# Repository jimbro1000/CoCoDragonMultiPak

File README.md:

# Dragon MultiPak Interface #

This repository contains the designs for a Dragon 32/64
multipak interface based closely on the TRS-80 Color 
Computer multipak system.

The board allows up to four expansion cartridges to be
connected instead of the normal single slot.

The original CoCo MultiPak is a poor fit with the 
Dragon, this design slims down the interface to
ensure it will work with the Dragon cartridge port.

The CoCo also includes a -5V rail connection which
the Dragon substitutes with an additional +12V rail.
Both cartridge pins are unconnected in this design
as a precaution

## Power Supply ##

For casual use the +5V supplied by the Dragon PSU
should suffice but could become marginal under load.
This board includes an independent power supply that
can supplement the 5V current supply, or even run a
modified Dragon board if additional voltages are not
required.

The power board requires either a 12-15V AC input or
a 15-18V DC input (polarity of the connector is not
important). If 12V is not required (or critical) a 
lower rated DC power adapter can be used.

By default the 12V rail is rated at 0.5A but the 
DC-DC converter on the board can easily be swapped
for a higher rated compatible component.

## GAL Programming ##

A comprehensive set of source definitions for the 
GAL 16V8 chip at IC13 are available on github:
https://github.com/TheLittleEngineers/CoCoDragon-MultiPakInterface-CC-Multi-Pak_Version_1.2/tree/master/PAL_GAL

The GAL programs have been tested for use in a
CoCo but not with a Dragon - memory mapping should
be compatible so no issue is envisaged

Until testing is completed and the programming
conirmed the GAL programs should be treated as untried
in this context.

### GAL Equations

Note this is written in CUPL.

AND is &, OR is # and XOR is $

```CUPL
/** INPUT **/
PIN [2..9] = [A7..0];   /* address bus lsb */
PIN 1 = !FFXX;          /* mapped address range */
PIN 11 = RW;            /* RnW */
PIN 12 = E;             /* Quadrature clock E */
PIN 13 = Q;             /* Quadrature clock Q */
PIN 17 = !CSEL;         /* Cartridge select */
PIN 18 = !SLEB;         /* Device select disable */

/** OUTPUT **/
PIN 14 = !DBEN;         /* Enable data buffer */
PIN 15 = !IOR;          /* Read device select latch */
PIN 16 = !IOW;          /* Write device select latch */

/** EQUATIONS **/
FIELD ADDRESS = [A7..0];

MATCH = ADDRESS:[7F];

LATCH = MATCH & E & FFXX;

EN = ADDRESS:[40..7F] & FFXX;

DBEN = EN # SLEB # CSEL;

IOR = LATCH & RW;

IOW = LATCH & !Q & !RW;
```

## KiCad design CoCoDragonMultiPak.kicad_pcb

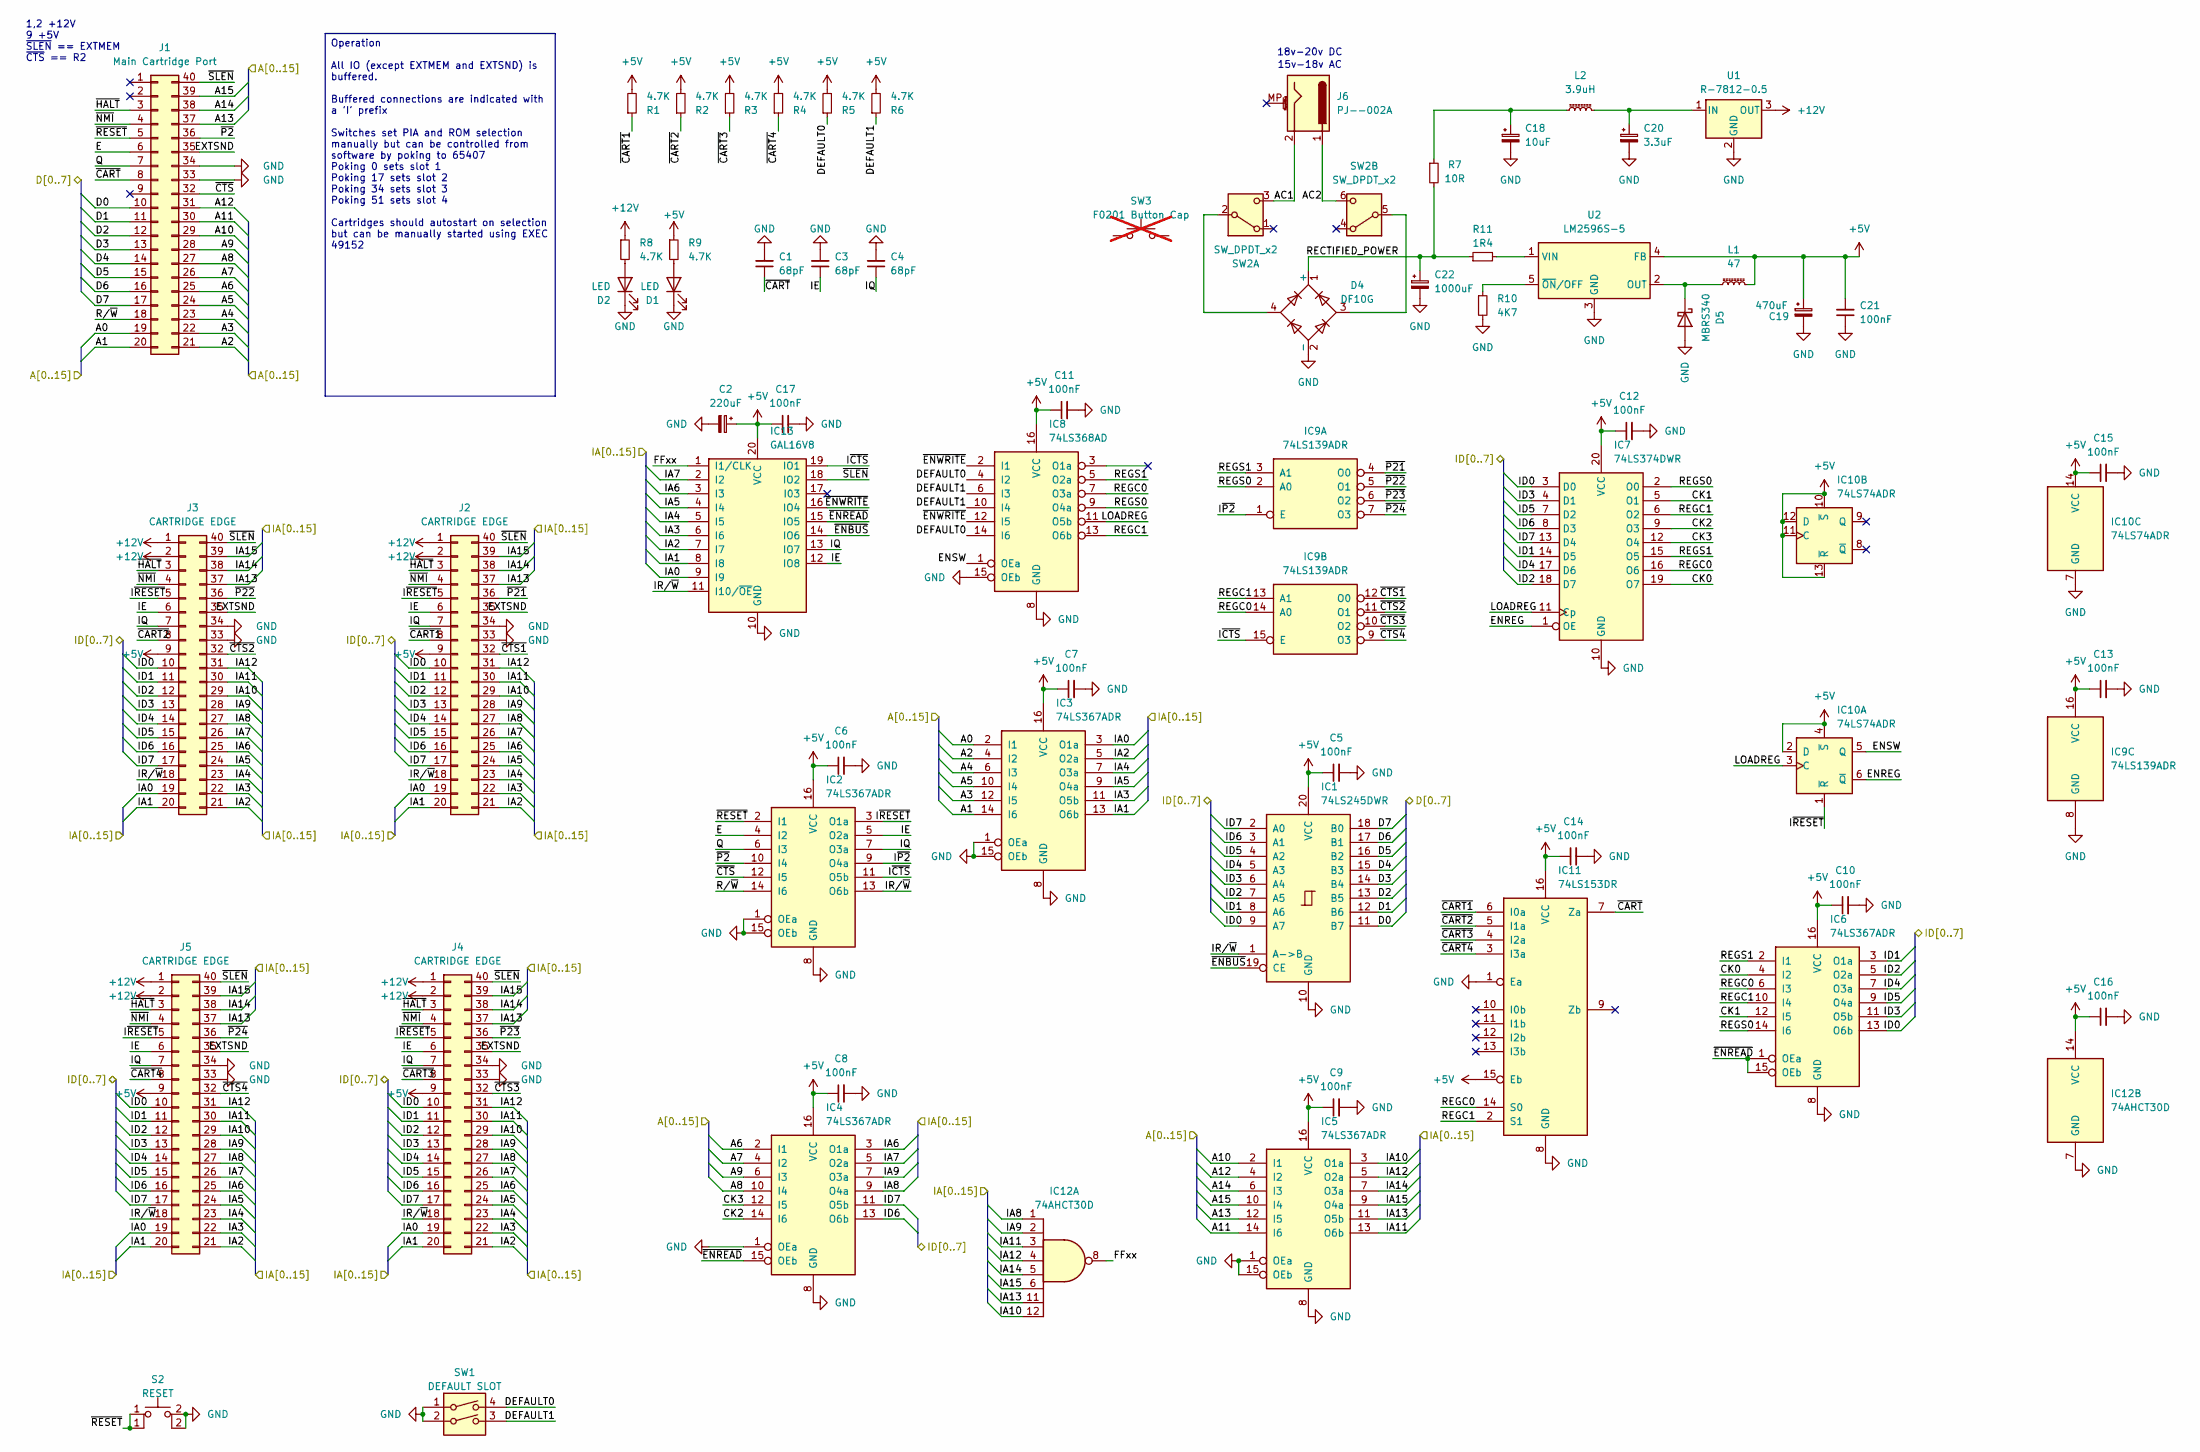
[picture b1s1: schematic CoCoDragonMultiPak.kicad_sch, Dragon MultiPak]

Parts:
C1, C3, C4: 68pF; C_0805_2012Metric_Pad1.18x1.45mm_HandSolder; LCSC C2363555
C2: 220uF; CP_Elec_6.3x5.4_Nichicon; LCSC C2162905
C5, C6, C7, C8, C9, C10, C11, C12, C13, C14, C15, C16, C17: 100nF; C_0805_2012Metric_Pad1.18x1.45mm_HandSolder; LCSC C2215757
C18: 10uF; CP_Elec_4x5.4; LCSC C213486
C19: 470uF; CP_Elec_6.3x5.4_Nichicon
C20: 3.3uF; CP_Elec_4x5.8; LCSC C413673
C21: 100nF; C_0805_2012Metric_Pad1.18x1.45mm_HandSolder
C22: 1000uF; CP_Elec_10x10.5
D1, D2: LED; LED_0805_2012Metric_Pad1.15x1.40mm_HandSolder; LCSC C5353441
D4: DF10G; Diode_Bridge_DIP-4_W7.62mm_P5.08mm; DigiKey 641-1340-5-ND
D5: MBRS340; D_SMC_Handsoldering; DigiKey 112-VS-MBRS340-M3/9ATCT-ND
IC1: 74LS245DWR; SOIC-20W_7.5x12.8mm_P1.27mm; DigiKey 296-1125-1-ND
IC2, IC3, IC4, IC5, IC6: 74LS367ADR; SOIC-16_3.9x9.9mm_P1.27mm; DigiKey 296-3700-1-ND
IC7: 74LS374DWR; SOIC-20W_7.5x12.8mm_P1.27mm; DigiKey 296-14894-1-ND
IC8: 74LS368AD; SOIC-16_3.9x9.9mm_P1.27mm; DigiKey 296-33998-5-ND
IC9: 74LS139ADR; SOIC-16_3.9x9.9mm_P1.27mm; DigiKey 296-31850-1-ND
IC10: 74LS74ADR; SOIC-14_3.9x8.7mm_P1.27mm; DigiKey 296-14899-1-ND
IC11: 74LS153DR; SOIC-16_3.9x9.9mm_P1.27mm; DigiKey 296-SN74LS153DRCT-ND
IC12: 74AHCT30D; SOIC-14_3.9x8.7mm_P1.27mm; DigiKey 1727-74AHCT30D-Q100JCT-ND
IC13: GAL16V8; DIP-20_W7.62mm_LongPads; DigiKey ATF16V8C-7PU-ND
J1: Main Cartridge Port; EdgeConnector
J2, J3, J4, J5: CARTRIDGE EDGE; CardSocket; DigiKey 3-583717-1-ND
J6: PJ--002A; Power_BarrelJack; DigiKey CP-002A-ND
L1: 47; L_Taiyo-Yuden_MD-4040; LCSC C520312
L2: 3.9uH; L_1812_4532Metric; LCSC C5603190
R1, R2, R3, R4, R5, R6, R8, R9: 4.7K; R_0805_2012Metric_Pad1.20x1.40mm_HandSolder; LCSC C269341
R7: 10R; R_2512_6332Metric; LCSC C2992634
R10: 4K7; R_0805_2012Metric_Pad1.20x1.40mm_HandSolder; LCSC C706300
R11: 1R4; RES_SM6227_STP; LCSC C4075361
S2: RESET; SW_PUSH_6mm; DigiKey 450-1644-ND
SW1: DEFAULT SLOT; SW_DIP_SPSTx02_Slide_6.7x6.64mm_W7.62mm_P2.54mm_LowProfile; DigiKey CT1952MST-ND
SW2: SW_DPDT_x2; ALPS_DPDT_SPUN190900
SW3: F0201 Button Cap; SW_PUSH-12mm; DigiKey 401-1215-ND; not fitted
U1: R-7812-0.5; Converter_DCDC_RECOM_R-78E-0.5_THT; DigiKey 945-1032-ND
U2: LM2596S-5; TO-263-5_TabPin3; DigiKey LM2596S-5.0/NOPB-ND

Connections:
+5V: C2.1, C5.1, C6.1, C7.1, C8.1, C9.1, C10.1, C11.1, C12.1, C13.1, C14.1, C15.1, C16.1, C17.1, C19.1, C21.2, IC1.20 (VCC), IC2.16 (VCC), IC3.16 (VCC), IC4.16 (VCC), IC5.16 (VCC), IC6.16 (VCC), IC7.20 (VCC), IC8.16 (VCC), IC9.16 (VCC), IC10.2 (D), IC10.4 (~S), IC10.10 (~S), IC10.11 (C), IC10.12 (D), IC10.13 (~R), IC10.14 (VCC), IC11.15 (Eb), IC11.16 (VCC), IC12.14 (VCC), IC13.20 (VCC), J2.9, J3.9, J4.9, J5.9, L1.2, R1.2, R2.2, R3.2, R4.2, R5.2, R6.2, R9.1, U2.4 (FB)
+12V: J2.1, J2.2, J3.1, J3.2, J4.1, J4.2, J5.1, J5.2, R8.1, U1.3 (OUT)
/A0: IC3.2 (I1), J1.19
/A1: IC3.14 (I6), J1.20
/A2: IC3.4 (I2), J1.21
/A3: IC3.12 (I5), J1.22
/A4: IC3.6 (I3), J1.23
/A5: IC3.10 (I4), J1.24
/A6: IC4.2 (I1), J1.25
/A7: IC4.4 (I2), J1.26
/A8: IC4.10 (I4), J1.27
/A9: IC4.6 (I3), J1.28
/A10: IC5.2 (I1), J1.29
/A11: IC5.14 (I6), J1.30
/A12: IC5.4 (I2), J1.31
/A13: IC5.12 (I5), J1.37
/A14: IC5.6 (I3), J1.38
/A15: IC5.10 (I4), J1.39
/AC1: J6.2, SW2.3 (C)
/AC2: J6.1, SW2.6 (C)
/CK0: IC6.4 (I2), IC7.19 (O7)
/CK1: IC6.12 (I5), IC7.5 (O1)
/CK2: IC4.14 (I6), IC7.9 (O3)
/CK3: IC4.12 (I5), IC7.12 (O4)
/D0: IC1.11 (B7), J1.10
/D1: IC1.12 (B6), J1.11
/D2: IC1.13 (B5), J1.12
/D3: IC1.14 (B4), J1.13
/D4: IC1.15 (B3), J1.14
/D5: IC1.16 (B2), J1.15
/D6: IC1.17 (B1), J1.16
/D7: IC1.18 (B0), J1.17
/DEFAULT0: IC8.4 (I2), IC8.14 (I6), R5.1, SW1.4
/DEFAULT1: IC8.6 (I3), IC8.10 (I4), R6.1, SW1.3
/E: IC2.4 (I2), J1.6
/ENREG: IC7.1 (OE), IC10.6 (~Q)
/ENSW: IC8.1 (OEa), IC10.5 (Q)
/EXTSND: J1.35, J2.35, J3.35, J4.35, J5.35
/FFxx: IC12.8, IC13.1 (I1/CLK)
/IA0: IC3.3 (O1a), IC13.9 (I9), J2.19, J3.19, J4.19, J5.19
/IA1: IC3.13 (O6b), IC13.8 (I8), J2.20, J3.20, J4.20, J5.20
/IA2: IC3.5 (O2a), IC13.7 (I7), J2.21, J3.21, J4.21, J5.21
/IA3: IC3.11 (O5b), IC13.6 (I6), J2.22, J3.22, J4.22, J5.22
/IA4: IC3.7 (O3a), IC13.5 (I5), J2.23, J3.23, J4.23, J5.23
/IA5: IC3.9 (O4a), IC13.4 (I4), J2.24, J3.24, J4.24, J5.24
/IA6: IC4.3 (O1a), IC13.3 (I3), J2.25, J3.25, J4.25, J5.25
/IA7: IC4.5 (O2a), IC13.2 (I2), J2.26, J3.26, J4.26, J5.26
/IA8: IC4.9 (O4a), IC12.1, J2.27, J3.27, J4.27, J5.27
/IA9: IC4.7 (O3a), IC12.2, J2.28, J3.28, J4.28, J5.28
/IA10: IC5.3 (O1a), IC12.12, J2.29, J3.29, J4.29, J5.29
/IA11: IC5.13 (O6b), IC12.3, J2.30, J3.30, J4.30, J5.30
/IA12: IC5.5 (O2a), IC12.4, J2.31, J3.31, J4.31, J5.31
/IA13: IC5.11 (O5b), IC12.11, J2.37, J3.37, J4.37, J5.37
/IA14: IC5.7 (O3a), IC12.5, J2.38, J3.38, J4.38, J5.38
/IA15: IC5.9 (O4a), IC12.6, J2.39, J3.39, J4.39, J5.39
/ID0: IC1.9 (A7), IC6.13 (O6b), IC7.3 (D0), J2.10, J3.10, J4.10, J5.10
/ID1: IC1.8 (A6), IC6.3 (O1a), IC7.14 (D5), J2.11, J3.11, J4.11, J5.11
/ID2: IC1.7 (A5), IC6.5 (O2a), IC7.18 (D7), J2.12, J3.12, J4.12, J5.12
/ID3: IC1.6 (A4), IC6.11 (O5b), IC7.4 (D1), J2.13, J3.13, J4.13, J5.13
/ID4: IC1.5 (A3), IC6.7 (O3a), IC7.17 (D6), J2.14, J3.14, J4.14, J5.14
/ID5: IC1.4 (A2), IC6.9 (O4a), IC7.7 (D2), J2.15, J3.15, J4.15, J5.15
/ID6: IC1.3 (A1), IC4.13 (O6b), IC7.8 (D3), J2.16, J3.16, J4.16, J5.16
/ID7: IC1.2 (A0), IC4.11 (O5b), IC7.13 (D4), J2.17, J3.17, J4.17, J5.17
/IE: C3.1, IC2.5 (O2a), IC13.12 (IO8), J2.6, J3.6, J4.6, J5.6
/IQ: C4.1, IC2.7 (O3a), IC13.13 (IO7), J2.7, J3.7, J4.7, J5.7
/IR/~W: IC1.1 (A->B), IC2.13 (O6b), IC13.11 (I10/~OE), J2.18, J3.18, J4.18, J5.18
/I~CTS: IC2.11 (O5b), IC9.15 (E), IC13.19 (IO1)
/I~P2: IC2.9 (O4a), IC9.1 (E)
/I~RESET: IC2.3 (O1a), IC10.1 (~R), J2.5, J3.5, J4.5, J5.5
/LOADREG: IC7.11 (Cp), IC8.11 (O5b), IC10.3 (C)
/Q: IC2.6 (I3), J1.7
/RECTIFIED_POWER: C22.1, D4.1 (+), R7.2, R11.1
/REGC0: IC6.6 (I3), IC7.16 (O6), IC8.7 (O3a), IC9.14 (A0), IC11.14 (S0)
/REGC1: IC6.10 (I4), IC7.6 (O2), IC8.13 (O6b), IC9.13 (A1), IC11.2 (S1)
/REGS0: IC6.14 (I6), IC7.2 (O0), IC8.9 (O4a), IC9.2 (A0)
/REGS1: IC6.2 (I1), IC7.15 (O5), IC8.5 (O2a), IC9.3 (A1)
/R/~W: IC2.14 (I6), J1.18
/~CART1: IC11.6 (I0a), J2.8, R1.1
/~CART2: IC11.5 (I1a), J3.8, R2.1
/~CART3: IC11.4 (I2a), J4.8, R3.1
/~CART4: IC11.3 (I3a), J5.8, R4.1
/~CART: C1.1, IC11.7 (Za), J1.8
/~CTS1: IC9.12 (O0), J2.32
/~CTS2: IC9.11 (O1), J3.32
/~CTS3: IC9.10 (O2), J4.32
/~CTS4: IC9.9 (O3), J5.32
/~CTS: IC2.12 (I5), J1.32
/~ENBUS: IC1.19 (CE), IC13.14 (IO6)
/~ENREAD: IC4.15 (OEb), IC6.1 (OEa), IC6.15 (OEb), IC13.15 (IO5)
/~ENWRITE: IC8.2 (I1), IC8.12 (I5), IC13.16 (IO4)
/~HALT: J1.3, J2.3, J3.3, J4.3, J5.3
/~NMI: J1.4, J2.4, J3.4, J4.4, J5.4
/~P2: IC2.10 (I4), J1.36
/~P21: IC9.4 (O0), J2.36
/~P22: IC9.5 (O1), J3.36
/~P23: IC9.6 (O2), J4.36
/~P24: IC9.7 (O3), J5.36
/~RESET: IC2.2 (I1), J1.5, S2.1 (A)
/~SLEN: IC13.18 (IO2), J1.40, J2.40, J3.40, J4.40, J5.40
GND: C1.2, C2.2, C3.2, C4.2, C5.2, C6.2, C7.2, C8.2, C9.2, C10.2, C11.2, C12.2, C13.2, C14.2, C15.2, C16.2, C17.2, C18.2, C19.2, C20.2, C21.1, C22.2, D1.1 (K), D2.1 (K), D4.2 (-), D5.2 (A), IC1.10 (GND), IC2.1 (OEa), IC2.8 (GND), IC2.15 (OEb), IC3.1 (OEa), IC3.8 (GND), IC3.15 (OEb), IC4.1 (OEa), IC4.8 (GND), IC5.1 (OEa), IC5.8 (GND), IC5.15 (OEb), IC6.8 (GND), IC7.10 (GND), IC8.8 (GND), IC8.15 (OEb), IC9.8 (GND), IC10.7 (GND), IC11.1 (Ea), IC11.8 (GND), IC12.7 (GND), IC13.10 (GND), J1.33, J1.34, J2.33, J2.34, J3.33, J3.34, J4.33, J4.34, J5.33, J5.34, R10.2, S2.2 (B), SW1.1, SW1.2, U1.2 (GND), U2.3 (GND)
unnamed: C18.1, L2.1, R7.1
unnamed: D1.2 (A), R9.2
unnamed: D2.2 (A), R8.2
unnamed: D5.1 (K), L1.1, U2.2 (OUT)
unnamed: D4.4, SW2.2 (B)
unnamed: D4.3, SW2.5 (B)
unnamed: C20.1, L2.2, U1.1 (IN)
unnamed: R11.2, U2.1 (VIN)
unnamed: R10.1, U2.5 (~ON/OFF)

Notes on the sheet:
18v-20v DC
1,2 +12V 9 +5V ~{SLEN} == EXTMEM ~{CTS} == R2
15v-18v AC
Operation All IO (except EXTMEM and EXTSND) is buffered. Buffered connections are indicated with a 'I' prefix Switches set PIA and ROM selection manually but can be controlled from software by poking to 65407 Poking 0 sets slot 1 Poking 17 sets slot 2 Poking 34 sets slot 3 Poking 51 sets slot 4 Car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

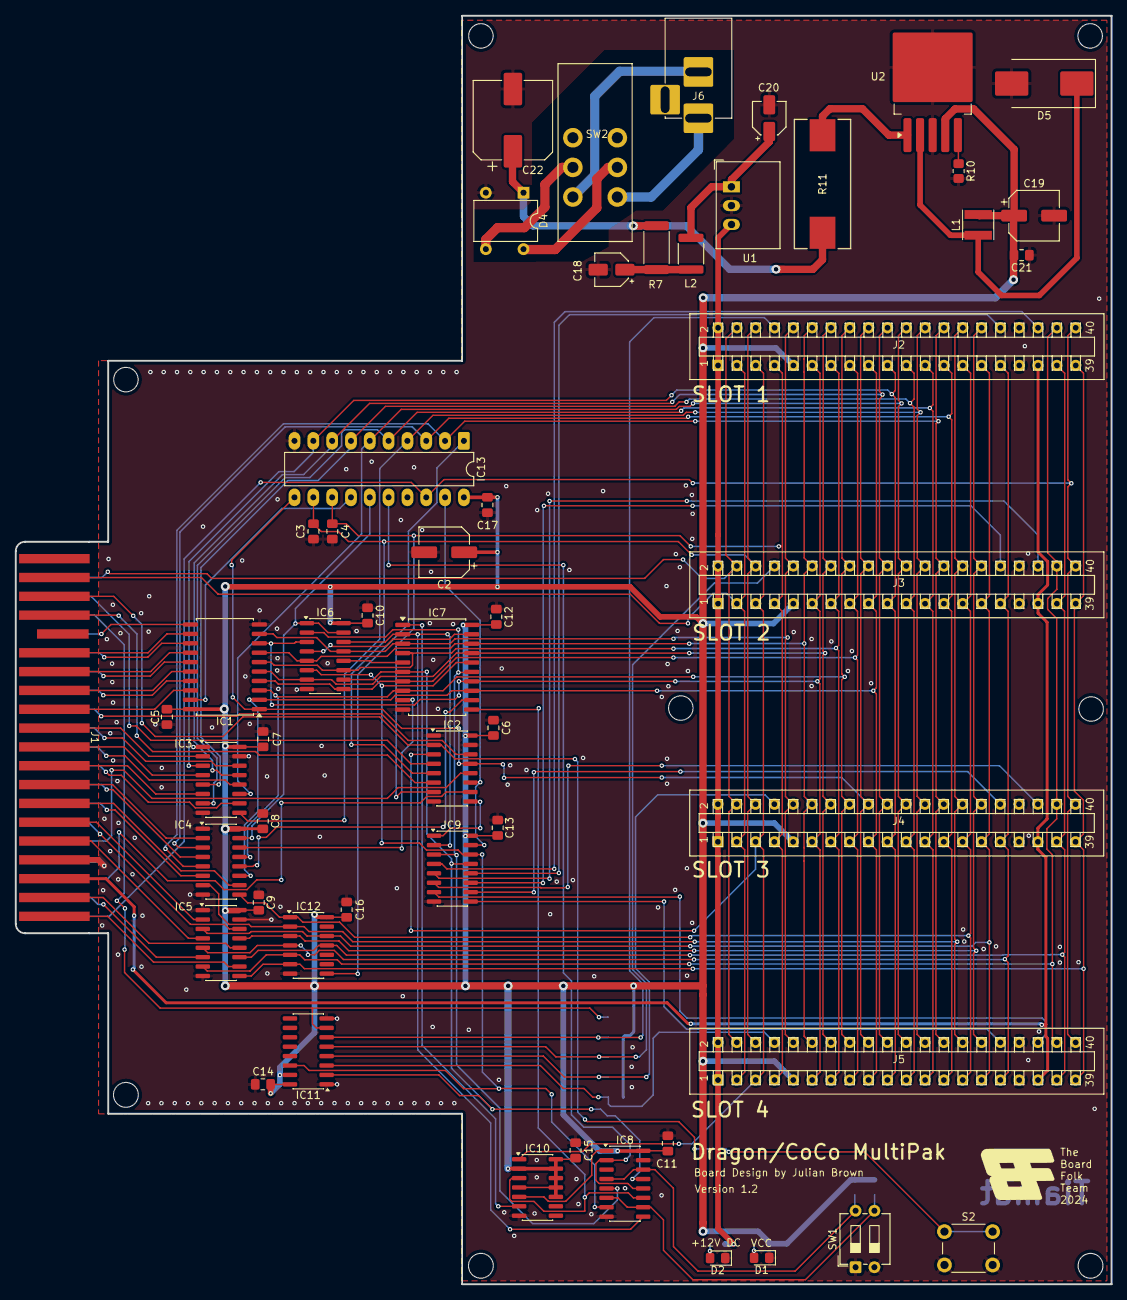
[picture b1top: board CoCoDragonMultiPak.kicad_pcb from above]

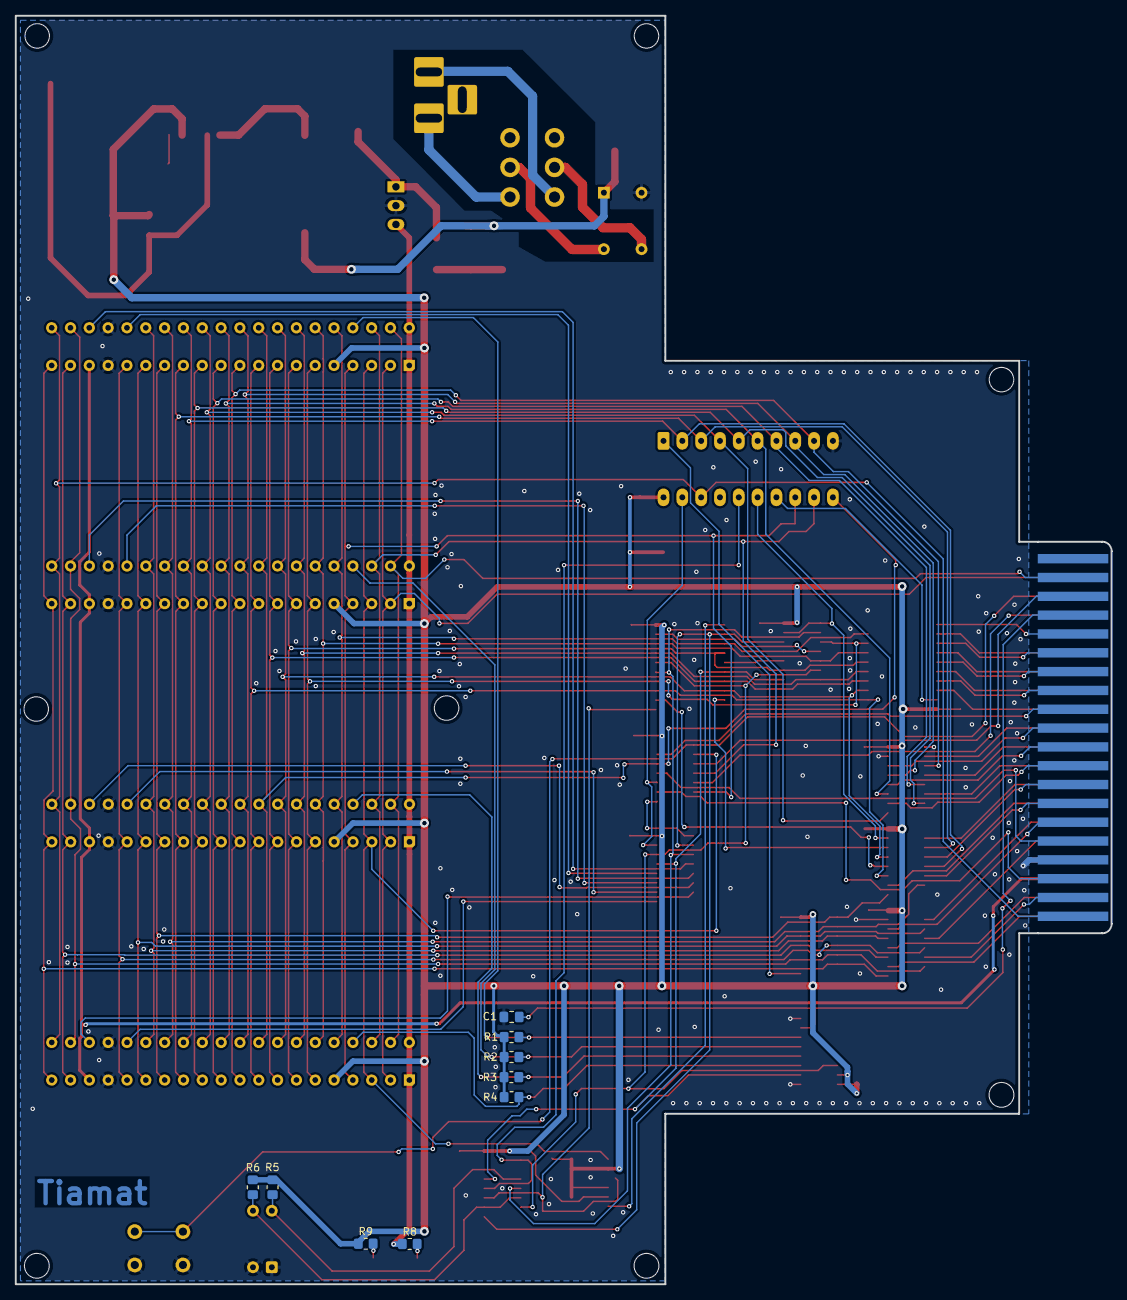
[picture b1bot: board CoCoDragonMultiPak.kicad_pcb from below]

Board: 2 copper layers, 147.9 x 171.2 mm, 64 parts (9 on the bottom side), 109 nets.

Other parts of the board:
Ge: LOGO; BoardFolk

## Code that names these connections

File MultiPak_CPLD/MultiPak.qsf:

# -------------------------------------------------------------------------- #
#
# Copyright (C) 1991-2013 Altera Corporation
# Your use of Altera Corporation's design tools, logic functions 
# and other software and tools, and its AMPP partner logic 
# functions, and any output files from any of the foregoing 
# (including device programming or simulation files), and any 
# associated documentation or information are expressly subject 
# to the terms and conditions of the Altera Program License 
# Subscription Agreement, Altera MegaCore Function License 
# Agreement, or other applicable license agreement, including, 
# without limitation, that your use is for the sole purpose of 
# programming logic devices manufactured by Altera and sold by 
# Altera or its authorized distributors.  Please refer to the 
# applicable agreement for further details.
#
# -------------------------------------------------------------------------- #
#
# Quartus II 64-Bit
# Version 13.0.1 Build 232 06/12/2013 Service Pack 1 SJ Web Edition
# Date created = 15:19:12  June 15, 2025
#
# -------------------------------------------------------------------------- #
#
# Notes:
#
# 1) The default values for assignments are stored in the file:
#		MultiPak_assignment_defaults.qdf
#    If this file doesn't exist, see file:
#		assignment_defaults.qdf
#
# 2) Altera recommends that you do not modify this file. This
#    file is updated automatically by the Quartus II software
#    and any changes you make may be lost or overwritten.
#
# -------------------------------------------------------------------------- #


set_global_assignment -name FAMILY MAX7000S
set_global_assignment -name DEVICE "EPM7128SQC100-6"
set_global_assignment -name TOP_LEVEL_ENTITY MultiPak
set_global_assignment -name ORIGINAL_QUARTUS_VERSION "13.0 SP1"
set_global_assignment -name PROJECT_CREATION_TIME_DATE "15:19:12  JUNE 15, 2025"
set_global_assignment -name LAST_QUARTUS_VERSION "13.0 SP1"
set_global_assignment -name PROJECT_OUTPUT_DIRECTORY output_files
set_global_assignment -name DEVICE_FILTER_PACKAGE "ANY QFP"
set_global_assignment -name ERROR_CHECK_FREQUENCY_DIVISOR "-1"
set_global_assignment -name MIN_CORE_JUNCTION_TEMP 0
set_global_assignment -name MAX_CORE_JUNCTION_TEMP 85
set_global_assignment -name EDA_DESIGN_ENTRY_SYNTHESIS_TOOL "Design Compiler"
set_global_assignment -name EDA_INPUT_VCC_NAME VDD -section_id eda_design_synthesis
set_global_assignment -name EDA_LMF_FILE altsyn.lmf -section_id eda_design_synthesis
set_global_assignment -name EDA_INPUT_DATA_FORMAT EDIF -section_id eda_design_synthesis
set_global_assignment -name EDA_SIMULATION_TOOL "ModelSim (Verilog)"
set_global_assignment -name EDA_TIME_SCALE "1 ps" -section_id eda_simulation
set_global_assignment -name EDA_OUTPUT_DATA_FORMAT "VERILOG HDL" -section_id eda_simulation
set_global_assignment -name VERILOG_FILE MultiPak.v
set_global_assignment -name MAX7000_DEVICE_IO_STANDARD "3.3-V LVTTL"
set_global_assignment -name VERILOG_FILE DFF.v
set_global_assignment -name DEVICE_FILTER_PIN_COUNT 100
set_global_assignment -name VERILOG_FILE DataLatch.v
set_global_assignment -name VERILOG_FILE Demux42.v
set_global_assignment -name VERILOG_FILE Mux41.v
set_global_assignment -name VERILOG_FILE TriBuffer.v
set_global_assignment -name VERILOG_FILE TriInvBuffer.v
set_location_assignment PIN_1 -to A[0]
set_location_assignment PIN_2 -to A[1]
set_location_assignment PIN_3 -to A[2]
set_location_assignment PIN_4 -to A[3]
set_location_assignment PIN_7 -to A[4]
set_location_assignment PIN_8 -to A[5]
set_location_assignment PIN_6 -to TDI
set_location_assignment PIN_9 -to A[6]
set_location_assignment PIN_10 -to A[7]
set_location_assignment PIN_11 -to A[8]
set_location_assignment PIN_12 -to A[9]
set_location_assignment PIN_14 -to A[10]
set_location_assignment PIN_15 -to A[11]
set_location_assignment PIN_16 -to A[12]
set_location_assignment PIN_17 -to TMS
set_location_assignment PIN_21 -to A[13]
set_location_assignment PIN_22 -to A[14]
set_location_assignment PIN_23 -to A[15]
set_location_assignment PIN_100 -to D[7]
set_location_assignment PIN_99 -to D[6]
set_location_assignment PIN_98 -to D[5]
set_location_assignment PIN_96 -to D[4]
set_location_assignment PIN_95 -to D[3]
set_location_assignment PIN_94 -to D[2]
set_location_assignment PIN_87 -to D[1]
set_location_assignment PIN_86 -to D[0]
set_location_assignment PIN_64 -to TCK
set_location_assignment PIN_75 -to TDO
set_location_assignment PIN_85 -to iCART
set_location_assignment PIN_56 -to iP2
set_location_assignment PIN_82 -to iRESET
set_location_assignment PIN_81 -to RnW
set_location_assignment PIN_29 -to DEFAULT[1]
set_location_assignment PIN_30 -to DEFAULT[0]
set_location_assignment PIN_60 -to CART[3]
set_location_assignment PIN_65 -to CART[2]
set_location_assignment PIN_70 -to CTS[1]
set_location_assignment PIN_73 -to CTS[0]
set_location_assignment PIN_69 -to CART[1]
set_location_assignment PIN_72 -to CART[0]
set_location_assignment PIN_62 -to CTS[3]
set_location_assignment PIN_66 -to CTS[2]
set_location_assignment PIN_80 -to E
set_location_assignment PIN_79 -to Q
set_location_assignment PIN_63 -to P2[3]
set_location_assignment PIN_67 -to P2[2]
set_location_assignment PIN_71 -to P2[1]
set_location_assignment PIN_74 -to P2[0]
set_location_assignment PIN_59 -to IOW
set_location_assignment PIN_24 -to nCTS
set_location_assignment PIN_25 -to nSLEN

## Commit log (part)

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2024-05-10 convert to smd
2024-05-10 progress trace routing
2024-05-10 finish routing
2024-05-11 refine power circuit layout
2024-08-19 revise layout
2024-08-19 populate supplier specific part numbers
2025-06-15 switch gal for cpld
2025-06-16 convert to ATF1508
2025-08-01 revise gal cupl code to switch pins
2026-03-30 revise for production
